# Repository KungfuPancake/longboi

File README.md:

# Longboi AFC controller

Tired of the mess of cables in your BoxTurtle? Want to add a heated filament dryer chamber some time down the road? Want to control that cooling fan with PWM? This project is for you!

The Longboi sits behind the full width of the BoxTurtle front panel and allows very short cable runs of equal length from each respooler and extruder. It's equipped with a beefy STM32H723 MCU and can be controlled with CAN or USB. If using CAN it's also daisy chainable for 8, 12 or even more lanes!

# How to get a Longboi

## Buying a complete board
LDO will sell complete boards via various resellers. Production is currently unknown - check back later for updates!

## PCB + Assembly by JLCPCB
You can order assembled PCBs from pretty much any fab, although currently only production files tested with JLCPCB are available in [jlcpcb/](https://github.com/KungfuPancake/longboi/tree/main/jlcpcb).
To order PCBs with assembly you'll have to go through their manufacturing wizard, using mostly standard settings. Although the JLC engineers will try and correct any mistakes, please do sanity checks on every page.
1. Upload `longboi.zip`into the PCB quote form and select a quantity. Five PCBs is the minimum quantity, cost per board will be lower the more boards you order since most of the cost is setup fees. Select a solder mask color you like - green is usually cheapest. I highly recommend choosing ENIG as a surface finish, HASL is usually not worth the saved money on production boards. Leave all other settings on their default values. Check PCBA (assembly) on the bottom of the form. Click "Next".
2. Check if the PCB looks like it should, then click "Next".
3. Upload `bom.csv` for BOM, `positions.csv`for CPL. Click "Next".
4. Check if all components look right, if there are stock shortages you will have to select replacement. Be very careful to select components that are equal or better in specs. If everything looks good, click "Next".
5. Check the placement of all components, especially if the first pin corresponds with the PCB markings. Slight inaccuracies on the big through hole connectors are okay, as they are hand soldered anyway. Click "Next".
6. You'll see a breakdown of all individual fees and prices. If you're flexible on the amount of PCBs you order you can try and see which amount has the best value to you.
7. Done!

Please be aware that the BOM only contains a fuse holder, the fuses (2410/1808) have to be sourced separately. 4A is a good value to start, depending on the heater you may or may not use the value can be scaled up or down accordingly.

## PCB + assembling it yourself
Order the PCBs anywere you want as the specs are very modest. Assembly of the board is an advanced task requiring lots of soldering, including hot air and/or using a reflow oven. If you don't feel comfortable with that, you should let the fab handle the assembly.

Please be aware that the BOM only contains a fuse holder, the fuses (2410/1808) have to be sourced separately. 4A is a good value to start, depending on the heater you may or may not use the value can be scaled up or down accordingly.

# Preparations
This is a general guideline how to proceed with flashing the Katapult bootloader (optional) and Klipper. If you struggle with the process or encounter errors on the way, especially when using CAN bus, try the detailed instructions and troubleshooting tips and tricks from [Esoterical's CANBus guide](https://canbus.esoterical.online/).
Start with only USB connected via the JST header. When plugging in the USB cable into your computer, the 3.3V and USB LEDs should light up. Now you're ready for flashing!

## CAN
### Katapult

### Klipper

## USB
### Katapult

### Klipper

## Initial flash via DFU
To enable CAN or USB flashing via Katapult or Klipper you'll have to bootstrap the board via the MCUs built-in DFU bootloader, using dfu-util. To enter the DFU bootloader, hold down the "Boot"-button, then press the "Reset"-button shortly. You can now release both buttons and the Longboi should be visible as a "STM Device in DFU Mode" USB device.

Use dfu-util to flash the desired firmware, e.g. Katapult: ```dfu-util -R -a 0 -s 0x08000000:leave -D ~/katapult/out/katapult.bin -d 0483:df11```

## Flashing Katapult and/or Klipper
When using USB, flashing Katapult is not needed as Klipper can update its own firmware. Go through the Klipper build steps using the configuration from above, then flash klipper.bin using dfu-util. From now on you can update Klipper directly with ```make flash FLASH_DEVICE={your device path}```

If you're using a CAN setup and need to use Katapult, build it with the configuration from above and flash it via ```dfu-util```. You may have to reset the board with the "Reset"-button after flashing, the "Info"-LED should be blinking now. If it doesn't, try manually entering Katapult by double-clicking "Reset". Once Katapult is running, all flash operations have to be done via CAN bus. Remove the USB cable from the board and attach it to your CAN bus using a suitable cable. Remember to power down your printer before connecting anything!

If everything went well, Katapult should be visible with the flash tool: ```~/katapult/scripts/flashtool.py -i can0 -q```

You can now flash Klipper: ```~/katapult/scripts/flashtool.py -f ~/klipper/out/klipper.bin -u {your address}```

And you're done!

## Print parts
### Base BoxTurtle
BOM:
* ~95g of primary color filament
* 7x M3x4x5 heat set insert (Voron style)
* 7x M3x10 SHCS
* (Optional) 7x M3x5 brass standoffs
* (Optional) 7x M3x4 SHCS

Print the following parts in your primary color:

* 1x skirt_front_hex_single.stl (no split parts available yet)

If you're not using brass standoffs, also print:

* 7x pcb_spacer_x7.stl

Print all parts using the BoxTurtle settings, make sure that you tuned your filament for shrinkage as the mounting holes won't line up otherwise.

### BoxTurtle Enclosure
Please use the CAD files for reference until a detailed manual is available.

# Assembly
## Mounting PCB + front skirt
### Base BoxTurtle
Add the heat set inserts into the front skirt, then mount the PCB. If you're using brass standoffs, screw those in first, then mount the board using the M3x4 fasteners. If using printed spacers, for easier assembly you can pre-insert two M3x10s into the PCB, add spacers and then mount it on the front skirt. Then use tweezers to add spacers between the PCB and the skirt on the remaining holes and add the rest of the M3x10s.
Insert the front skirt according to the manual and double check that the cutouts on the PCB correspond to the respooler switch tabs.

### BoxTurtle Enclosure
Please use the CAD files for reference until a detailed manual is available.

## Connections
Every respooler + extruder has its own set of connectors on the PCB, e.g. M4, RGB4, S8, S7, STP4.

If you're making your own cables, to make your life easier, assemble one respooler and one extruder first with generous cable length. Mount everything, measure everything, cut and crimp all connections. Afterwards, remove the respooler and extruder and finish the other three sets outside of the BoxTurtle with your measurements.
Tidy up with cable ties/velcro straps as needed and plug in everything.

# Configuration
## Pin aliases / longboi.cfg
coming soon
## AFC configuration
coming soon

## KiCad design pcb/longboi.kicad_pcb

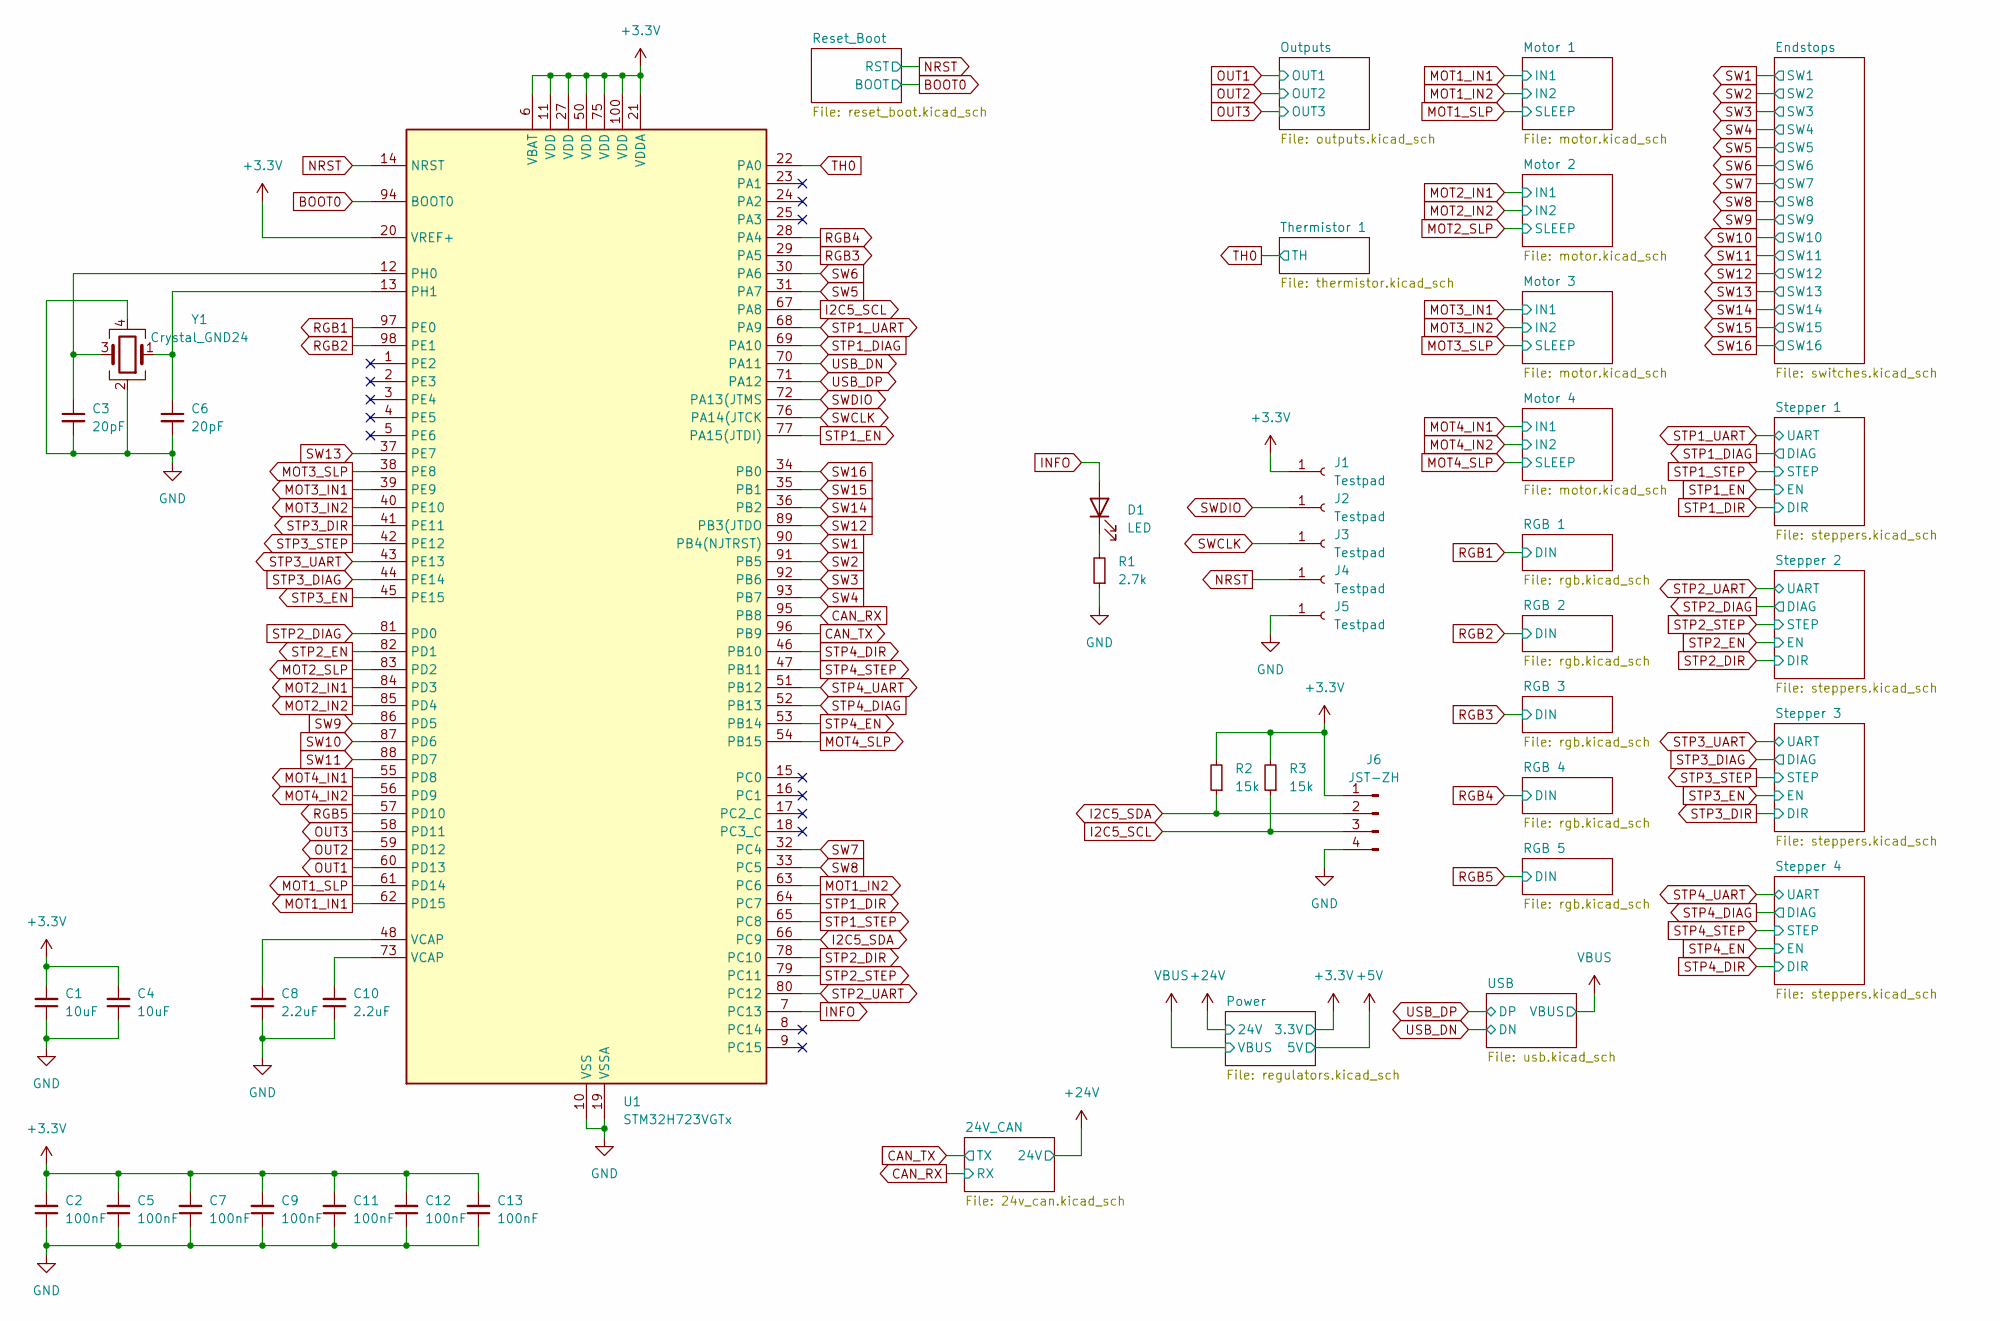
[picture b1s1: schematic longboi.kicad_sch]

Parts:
C1, C4: 10uF; C_0603_1608Metric
C2, C5, C7, C9, C11, C12, C13: 100nF; C_0603_1608Metric
C3, C6: 20pF; C_0603_1608Metric
C8, C10: 2.2uF; C_0603_1608Metric
D1: LED; LED_0603_1608Metric
J1, J2, J3, J4, J5: Testpad; TestPoint_THTPad_D1.0mm_Drill0.5mm
J6: JST-ZH; JST_ZH_B4B-ZR_1x04_P1.50mm_Vertical
R1: 2.7k; R_0603_1608Metric
R2, R3: 15k; R_0603_1608Metric
U1: STM32H723VGTx; LQFP-100_14x14mm_P0.5mm
Y1: Crystal_GND24; Crystal_SMD_3225-4Pin_3.2x2.5mm

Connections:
+3.3V: C1.2, C2.2, C4.2, C5.2, C7.2, C9.2, C11.2, C12.2, C13.2, J1.1, J6.1, R2.2, R3.2, U1.6 (VBAT), U1.11 (VDD), U1.20 (VREF+), U1.21 (VDDA), U1.27 (VDD), U1.50 (VDD), U1.75 (VDD), U1.100 (VDD); also elsewhere on the board
BOOT0: U1.94 (BOOT0); also elsewhere on the board
CAN_RX: U1.95 (PB8); also elsewhere on the board
CAN_TX: U1.96 (PB9); also elsewhere on the board
GND: C1.1, C2.1, C3.2, C4.1, C5.1, C6.2, C7.1, C8.1, C9.1, C10.1, C11.1, C12.1, C13.1, J5.1, J6.4, R1.1, U1.10 (VSS), U1.19 (VSSA), U1.26 (VSS), U1.49 (VSS), U1.74 (VSS), U1.99 (VSS), Y1.2, Y1.4; also elsewhere on the board
I2C5_SCL: J6.3, R3.1, U1.67 (PA8)
I2C5_SDA: J6.2, R2.1, U1.66 (PC9)
INFO: D1.2 (A), U1.7 (PC13)
MOT1_IN1: U1.62 (PD15); also elsewhere on the board
MOT1_IN2: U1.63 (PC6); also elsewhere on the board
MOT1_SLP: U1.61 (PD14); also elsewhere on the board
MOT2_IN1: U1.84 (PD3); also elsewhere on the board
MOT2_IN2: U1.85 (PD4); also elsewhere on the board
MOT2_SLP: U1.83 (PD2); also elsewhere on the board
MOT3_IN1: U1.39 (PE9); also elsewhere on the board
MOT3_IN2: U1.40 (PE10); also elsewhere on the board
MOT3_SLP: U1.38 (PE8); also elsewhere on the board
MOT4_IN1: U1.55 (PD8); also elsewhere on the board
MOT4_IN2: U1.56 (PD9); also elsewhere on the board
MOT4_SLP: U1.54 (PB15); also elsewhere on the board
NRST: J4.1, U1.14 (NRST); also elsewhere on the board
unnamed: C8.2, U1.48 (VCAP)
unnamed: C10.2, U1.73 (VCAP)
unnamed: D1.1 (K), R1.2
unnamed: C3.1, U1.12 (PH0), Y1.3
unnamed: C6.1, U1.13 (PH1), Y1.1
OUT1: U1.60 (PD13); also elsewhere on the board
OUT2: U1.59 (PD12); also elsewhere on the board
OUT3: U1.58 (PD11); also elsewhere on the board
RGB1: U1.97 (PE0); also elsewhere on the board
RGB2: U1.98 (PE1); also elsewhere on the board
RGB3: U1.29 (PA5); also elsewhere on the board
RGB4: U1.28 (PA4); also elsewhere on the board
RGB5: U1.57 (PD10); also elsewhere on the board
STP1_DIAG: U1.69 (PA10); also elsewhere on the board
STP1_DIR: U1.64 (PC7); also elsewhere on the board
STP1_EN: U1.77 (PA15(JTDI)); also elsewhere on the board
STP1_STEP: U1.65 (PC8); also elsewhere on the board
STP1_UART: U1.68 (PA9); also elsewhere on the board
STP2_DIAG: U1.81 (PD0); also elsewhere on the board
STP2_DIR: U1.78 (PC10); also elsewhere on the board
STP2_EN: U1.82 (PD1); also elsewhere on the board
STP2_STEP: U1.79 (PC11); also elsewhere on the board
STP2_UART: U1.80 (PC12); also elsewhere on the board
STP3_DIAG: U1.44 (PE14); also elsewhere on the board
STP3_DIR: U1.41 (PE11); also elsewhere on the board
STP3_EN: U1.45 (PE15); also elsewhere on the board
STP3_STEP: U1.42 (PE12); also elsewhere on the board
STP3_UART: U1.43 (PE13); also elsewhere on the board
STP4_DIAG: U1.52 (PB13); also elsewhere on the board
STP4_DIR: U1.46 (PB10); also elsewhere on the board
STP4_EN: U1.53 (PB14); also elsewhere on the board
STP4_STEP: U1.47 (PB11); also elsewhere on the board
STP4_UART: U1.51 (PB12); also elsewhere on the board
SW1: U1.90 (PB4(NJTRST)); also elsewhere on the board
SW2: U1.91 (PB5); also elsewhere on the board
SW3: U1.92 (PB6); also elsewhere on the board
SW4: U1.93 (PB7); also elsewhere on the board
SW5: U1.31 (PA7); also elsewhere on the board
SW6: U1.30 (PA6); also elsewhere on the board
SW7: U1.32 (PC4); also elsewhere on the board
SW8: U1.33 (PC5); also elsewhere on the board
SW9: U1.86 (PD5); also elsewhere on the board
SW10: U1.87 (PD6); also elsewhere on the board
SW11: U1.88 (PD7); also elsewhere on the board
SW12: U1.89 (PB3(JTDO); also elsewhere on the board
SW13: U1.37 (PE7); also elsewhere on the board
SW14: U1.36 (PB2); also elsewhere on the board
SW15: U1.35 (PB1); also elsewhere on the board
SW16: U1.34 (PB0); also elsewhere on the board
SWCLK: J3.1, U1.76 (PA14(JTCK)
SWDIO: J2.1, U1.72 (PA13(JTMS)
TH0: U1.22 (PA0); also elsewhere on the board
USB_DN: U1.70 (PA11); also elsewhere on the board
USB_DP: U1.71 (PA12); also elsewhere on the board

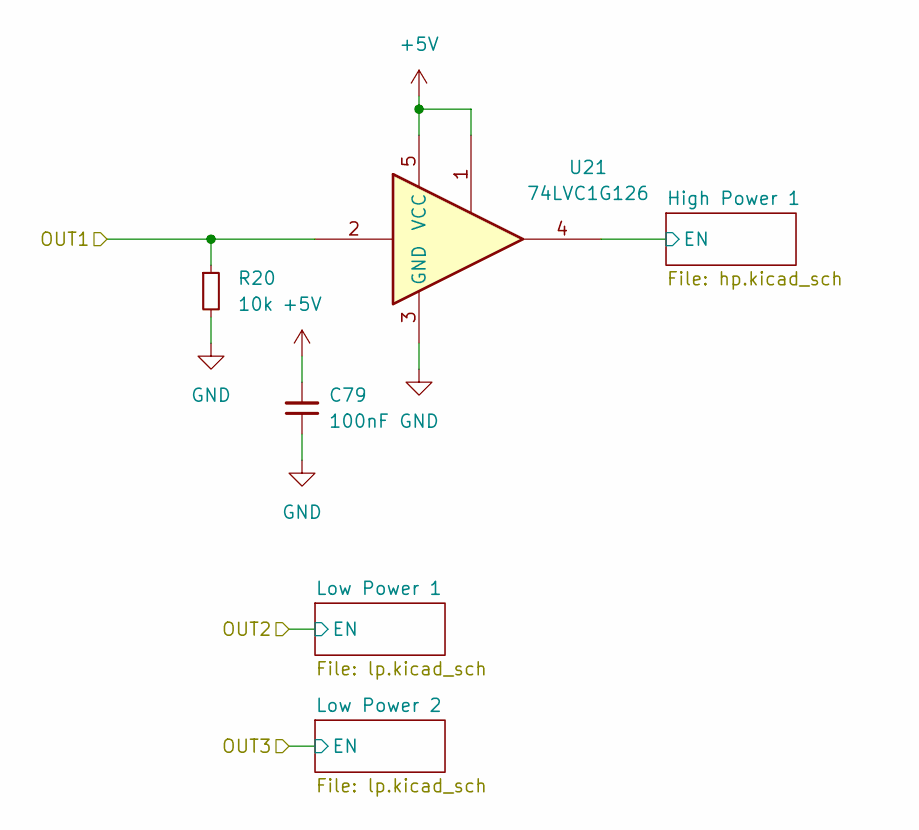
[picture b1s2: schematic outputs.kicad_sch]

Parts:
C79: 100nF; C_0603_1608Metric
R20: 10k; R_0603_1608Metric
U21: 74LVC1G126; SOT-353_SC-70-5

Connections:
+5V: C79.2, U21.1, U21.5 (VCC); also elsewhere on the board
/Outputs/High Power 1/EN: U21.4; also elsewhere on the board
GND: C79.1, R20.2, U21.3 (GND); also elsewhere on the board
OUT1: R20.1, U21.2; also elsewhere on the board

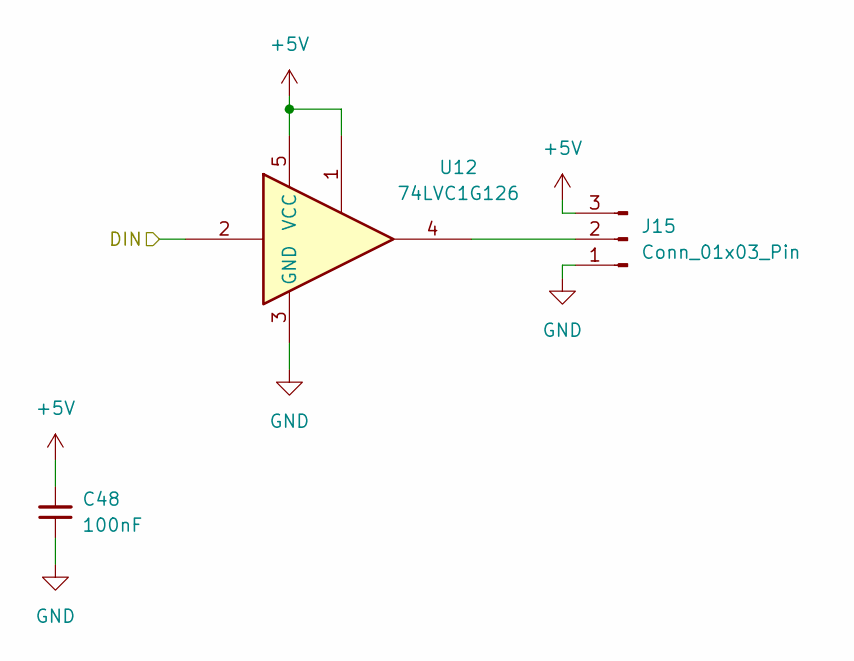
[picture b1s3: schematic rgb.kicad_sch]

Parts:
C48: 100nF; C_0603_1608Metric; LCSC C14663
J15: Conn_01x03_Pin; JST_XH_B3B-XH-A_1x03_P2.50mm_Vertical; LCSC C565985
U12: 74LVC1G126; SOT-353_SC-70-5; LCSC C7394032

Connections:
+5V: C48.2, J15.3, U12.1, U12.5 (VCC); also elsewhere on the board
GND: C48.1, J15.1, U12.3 (GND); also elsewhere on the board
unnamed: J15.2, U12.4
RGB1: U12.2; also elsewhere on the board

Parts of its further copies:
C49, C50, C51, C80: 100nF; C_0603_1608Metric; LCSC C14663
J16, J17, J18, J40: Conn_01x03_Pin; JST_XH_B3B-XH-A_1x03_P2.50mm_Vertical; LCSC C565985
U13, U14, U15, U22: 74LVC1G126; SOT-353_SC-70-5; LCSC C7394032

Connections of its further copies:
+5V: C49.2, C50.2, C51.2, C80.2, J16.3, J17.3, J18.3, J40.3, U13.1, U13.5 (VCC), U14.1, U14.5 (VCC), U15.1, U15.5 (VCC), U22.1, U22.5 (VCC); also elsewhere on the board
GND: C49.1, C50.1, C51.1, C80.1, J16.1, J17.1, J18.1, J40.1, U13.3 (GND), U14.3 (GND), U15.3 (GND), U22.3 (GND); also elsewhere on the board
unnamed: J16.2, U13.4
unnamed: J17.2, U14.4
unnamed: J18.2, U15.4
unnamed: J40.2, U22.4
RGB2: U13.2; also elsewhere on the board
RGB3: U14.2; also elsewhere on the board
RGB4: U15.2; also elsewhere on the board
RGB5: U22.2; also elsewhere on the board

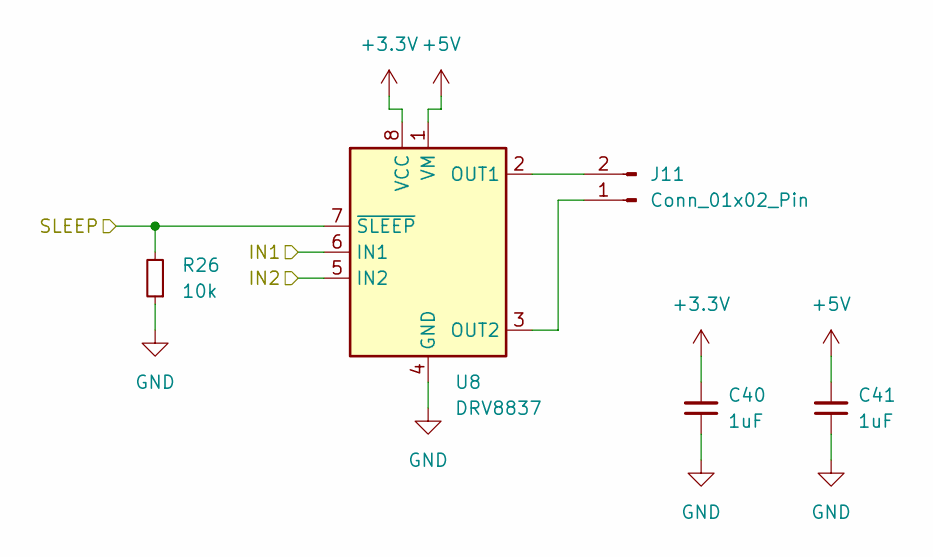
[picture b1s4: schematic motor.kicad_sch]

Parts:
C40, C41: 1uF; C_0603_1608Metric
J11: Conn_01x02_Pin; JST_XH_B2B-XH-A_1x02_P2.50mm_Vertical
R26: 10k; R_0603_1608Metric
U8: DRV8837; WSON-8-1EP_2x2mm_P0.5mm_EP0.9x1.6mm

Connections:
+3.3V: C40.2, U8.8 (VCC); also elsewhere on the board
+5V: C41.2, U8.1 (VM); also elsewhere on the board
GND: C40.1, C41.1, R26.1, U8.4 (GND), U8.9 (GND); also elsewhere on the board
MOT1_IN1: U8.6 (IN1); also elsewhere on the board
MOT1_IN2: U8.5 (IN2); also elsewhere on the board
MOT1_SLP: R26.2, U8.7 (~SLEEP); also elsewhere on the board
unnamed: J11.1, U8.3 (OUT2)
unnamed: J11.2, U8.2 (OUT1)

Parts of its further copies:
C42, C43, C44, C45, C46, C47: 1uF; C_0603_1608Metric
J12, J13, J14: Conn_01x02_Pin; JST_XH_B2B-XH-A_1x02_P2.50mm_Vertical
R27, R67, R68: 10k; R_0603_1608Metric
U9, U10, U11: DRV8837; WSON-8-1EP_2x2mm_P0.5mm_EP0.9x1.6mm

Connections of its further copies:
+3.3V: C42.2, C44.2, C46.2, U9.8 (VCC), U10.8 (VCC), U11.8 (VCC); also elsewhere on the board
+5V: C43.2, C45.2, C47.2, U9.1 (VM), U10.1 (VM), U11.1 (VM); also elsewhere on the board
GND: C42.1, C43.1, C44.1, C45.1, C46.1, C47.1, R27.1, R67.1, R68.1, U9.4 (GND), U9.9 (GND), U10.4 (GND), U10.9 (GND), U11.4 (GND), U11.9 (GND); also elsewhere on the board
MOT2_IN1: U9.6 (IN1); also elsewhere on the board
MOT2_IN2: U9.5 (IN2); also elsewhere on the board
MOT2_SLP: R27.2, U9.7 (~SLEEP); also elsewhere on the board
MOT3_IN1: U10.6 (IN1); also elsewhere on the board
MOT3_IN2: U10.5 (IN2); also elsewhere on the board
MOT3_SLP: R67.2, U10.7 (~SLEEP); also elsewhere on the board
MOT4_IN1: U11.6 (IN1); also elsewhere on the board
MOT4_IN2: U11.5 (IN2); also elsewhere on the board
MOT4_SLP: R68.2, U11.7 (~SLEEP); also elsewhere on the board
unnamed: J12.1, U9.3 (OUT2)
unnamed: J12.2, U9.2 (OUT1)
unnamed: J13.1, U10.3 (OUT2)
unnamed: J13.2, U10.2 (OUT1)
unnamed: J14.1, U11.3 (OUT2)
unnamed: J14.2, U11.2 (OUT1)

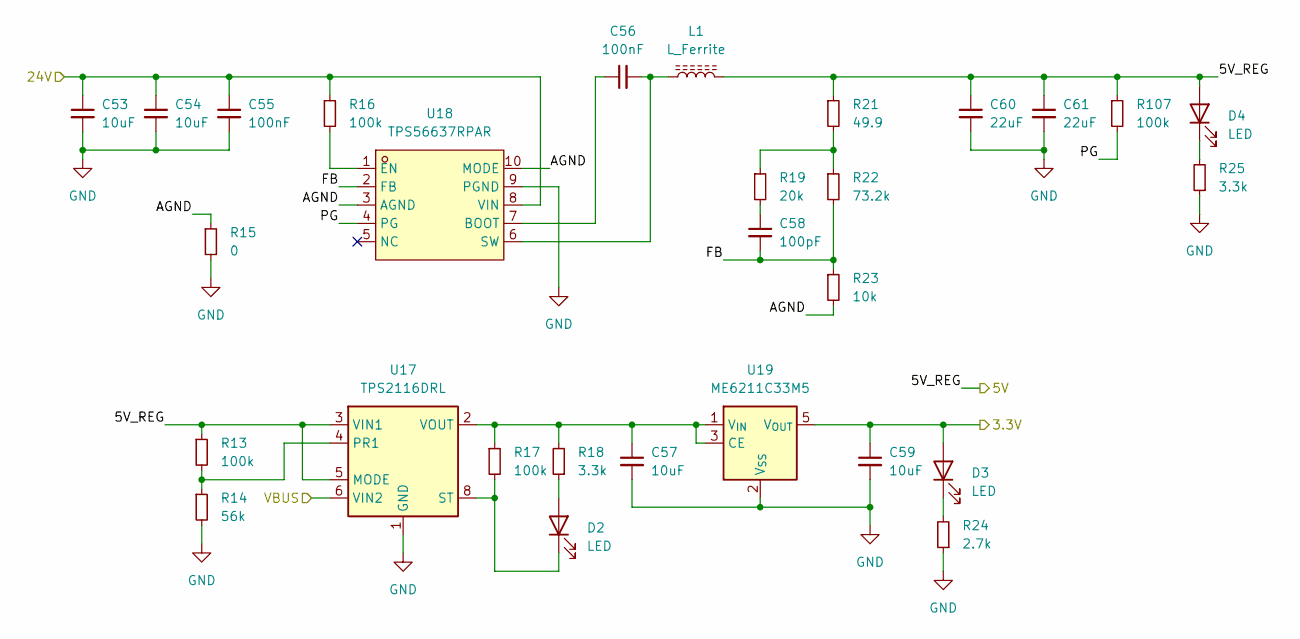
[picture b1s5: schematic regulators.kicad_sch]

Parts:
C53, C54: 10uF; C_1206_3216Metric
C55, C56: 100nF; C_0603_1608Metric
C57, C59: 10uF; C_0603_1608Metric
C58: 100pF; C_0603_1608Metric
C60, C61: 22uF; C_0805_2012Metric
D2, D3, D4: LED; LED_0603_1608Metric
L1: L_Ferrite; L_Chilisin_BMRA00050530
R13, R16, R17, R107: 100k; R_0603_1608Metric
R14: 56k; R_0603_1608Metric
R15: 0; R_0603_1608Metric
R18, R25: 3.3k; R_0603_1608Metric
R19: 20k; R_0603_1608Metric
R21: 49.9; R_0603_1608Metric
R22: 73.2k; R_0603_1608Metric
R23: 10k; R_0603_1608Metric
R24: 2.7k; R_0603_1608Metric
U17: TPS2116DRL; SOT-583-8
U18: TPS56637RPAR; VQFN-HR-10_L3.0-W3.0_RPA; LCSC Part C841386
U19: ME6211C33M5; SOT-23-5

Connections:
+3.3V: C59.1, D3.2 (A), U19.5 (V_{OUT}); also elsewhere on the board
+5V: C60.1, C61.1, D4.2 (A), L1.2, R13.1, R21.1, R107.1, U17.3 (VIN1), U17.5 (MODE); also elsewhere on the board
+24V: C53.1, C54.1, C55.1, R16.1, U18.8 (VIN); also elsewhere on the board
/Power/AGND: R15.1, R23.2, U18.3 (AGND), U18.10 (MODE)
/Power/FB: C58.2, R22.2, R23.1, U18.2 (FB)
/Power/PG: R107.2, U18.4 (PG)
GND: C53.2, C54.2, C55.2, C57.2, C59.2, C60.2, C61.2, R14.2, R15.2, R24.1, R25.1, U17.1 (GND), U18.9 (PGND), U19.2 (V_{SS}); also elsewhere on the board
unnamed: C58.1, R19.2
unnamed: D2.2 (A), R18.1
unnamed: D2.1 (K), R17.2, U17.8 (ST)
unnamed: D3.1 (K), R24.2
unnamed: D4.1 (K), R25.2
unnamed: R19.1, R21.2, R22.1
unnamed: R13.2, R14.1, U17.4 (PR1)
unnamed: C56.1, U18.7 (BOOT)
unnamed: R16.2, U18.1 (EN)
unnamed: C56.2, L1.1, U18.6 (SW)
unnamed: C57.1, R17.1, R18.2, U17.2 (VOUT), U17.7 (VOUT), U19.1 (V_{IN}), U19.3 (CE)
VBUS: U17.6 (VIN2); also elsewhere on the board

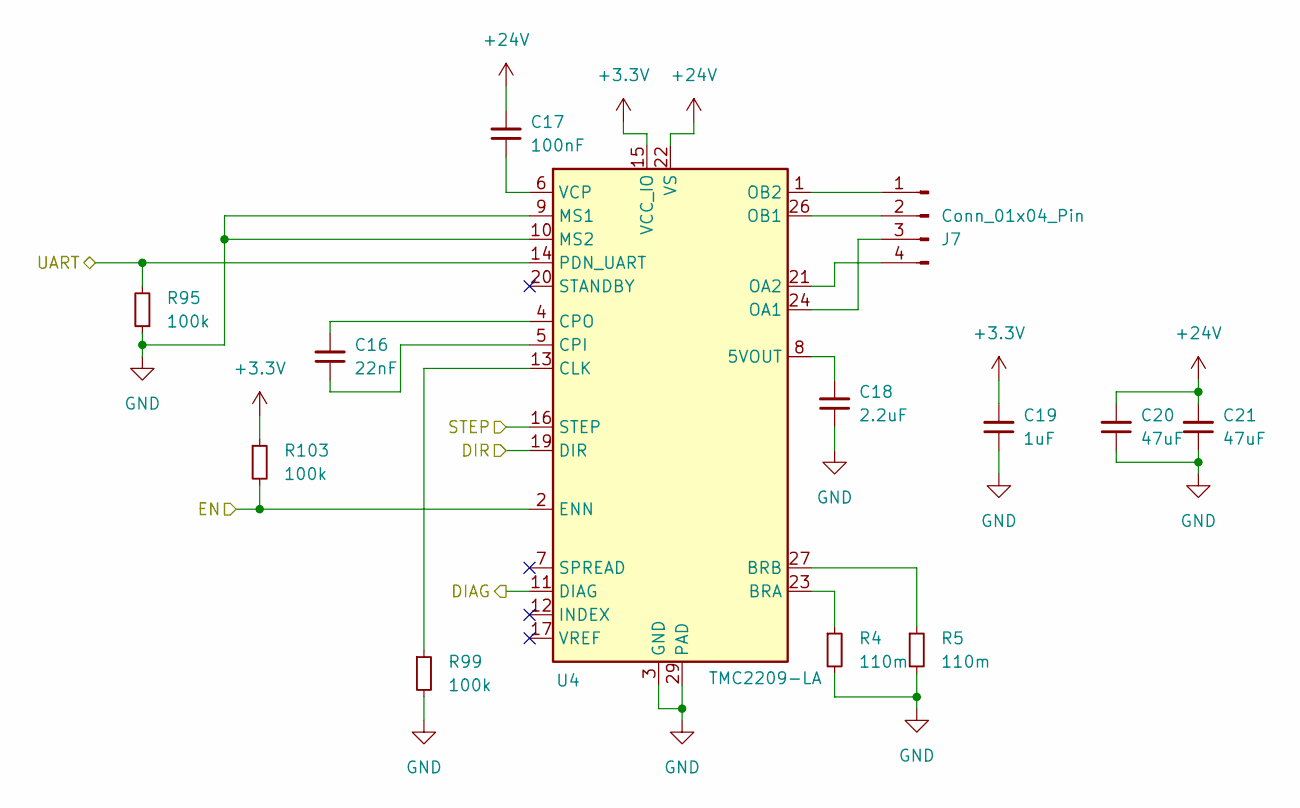
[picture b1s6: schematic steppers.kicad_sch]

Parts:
C16: 22nF; C_0603_1608Metric
C17: 100nF; C_0603_1608Metric
C18: 2.2uF; C_0603_1608Metric
C19: 1uF; C_0603_1608Metric
C20, C21: 47uF; C_1210_3225Metric
J7: Conn_01x04_Pin; JST_XH_B4B-XH-A_1x04_P2.50mm_Vertical
R4, R5: 110m; R_1206_3216Metric
R95, R99, R103: 100k; R_0603_1608Metric
U4: TMC2209-LA; QFN-28-1EP_5x5mm_P0.5mm_EP3.75x3.75mm_ThermalVias

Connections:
+3.3V: C19.2, R103.1, U4.15 (VCC_IO); also elsewhere on the board
+24V: C17.2, C20.2, C21.2, U4.22 (VS), U4.28 (VS); also elsewhere on the board
GND: C18.1, C19.1, C20.1, C21.1, R4.2, R5.2, R95.1, R99.2, U4.3 (GND), U4.9 (MS1), U4.10 (MS2), U4.18 (GND), U4.29 (PAD); also elsewhere on the board
unnamed: J7.1, U4.1 (OB2)
unnamed: J7.2, U4.26 (OB1)
unnamed: J7.3, U4.24 (OA1)
unnamed: J7.4, U4.21 (OA2)
unnamed: C18.2, U4.8 (5VOUT)
unnamed: R4.1, U4.23 (BRA)
unnamed: R5.1, U4.27 (BRB)
unnamed: R99.1, U4.13 (CLK)
unnamed: C16.1, U4.5 (CPI)
unnamed: C16.2, U4.4 (CPO)
unnamed: C17.1, U4.6 (VCP)
STP1_DIAG: U4.11 (DIAG); also elsewhere on the board
STP1_DIR: U4.19 (DIR); also elsewhere on the board
STP1_EN: R103.2, U4.2 (ENN); also elsewhere on the board
STP1_STEP: U4.16 (STEP); also elsewhere on the board
STP1_UART: R95.2, U4.14 (PDN_UART); also elsewhere on the board

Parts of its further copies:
C22, C28, C34: 22nF; C_0603_1608Metric
C23, C29, C35: 100nF; C_0603_1608Metric
C24, C30, C36: 2.2uF; C_0603_1608Metric
C25, C31, C37: 1uF; C_0603_1608Metric
C26, C27, C32, C33, C38, C39: 47uF; C_1210_3225Metric
J8, J9, J10: Conn_01x04_Pin; JST_XH_B4B-XH-A_1x04_P2.50mm_Vertical
R6, R7, R8, R9, R10, R11: 110m; R_1206_3216Metric
R96, R97, R98, R100, R101, R102, R104, R105, R106: 100k; R_0603_1608Metric
U5, U6, U7: TMC2209-LA; QFN-28-1EP_5x5mm_P0.5mm_EP3.75x3.75mm_ThermalVias

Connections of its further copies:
+3.3V: C25.2, C31.2, C37.2, R104.1, R105.1, R106.1, U5.15 (VCC_IO), U6.15 (VCC_IO), U7.15 (VCC_IO); also elsewhere on the board
+24V: C23.2, C26.2, C27.2, C29.2, C32.2, C33.2, C35.2, C38.2, C39.2, U5.22 (VS), U5.28 (VS), U6.22 (VS), U6.28 (VS), U7.22 (VS), U7.28 (VS); also elsewhere on the board
GND: C24.1, C25.1, C26.1, C27.1, C30.1, C31.1, C32.1, C33.1, C36.1, C37.1, C38.1, C39.1, R6.2, R7.2, R8.2, R9.2, R10.2, R11.2, R96.1, R97.1, R98.1, R100.2, R101.2, R102.2, U5.3 (GND), U5.9 (MS1), U5.10 (MS2), U5.18 (GND), U5.29 (PAD), U6.3 (GND), U6.9 (MS1), U6.10 (MS2), U6.18 (GND), U6.29 (PAD), U7.3 (GND), U7.9 (MS1), U7.10 (MS2), U7.18 (GND), U7.29 (PAD); also elsewhere on the board
unnamed: J8.1, U5.1 (OB2)
unnamed: J8.2, U5.26 (OB1)
unnamed: J8.3, U5.24 (OA1)
unnamed: J8.4, U5.21 (OA2)
unnamed: J9.1, U6.1 (OB2)
unnamed: J9.2, U6.26 (OB1)
unnamed: J9.3, U6.24 (OA1)
unnamed: J9.4, U6.21 (OA2)
unnamed: J10.1, U7.1 (OB2)
unnamed: J10.2, U7.26 (OB1)
unnamed: J10.3, U7.24 (OA1)
unnamed: J10.4, U7.21 (OA2)
unnamed: C24.2, U5.8 (5VOUT)
unnamed: R6.1, U5.23 (BRA)
unnamed: R7.1, U5.27 (BRB)
unnamed: R100.1, U5.13 (CLK)
unnamed: C22.1, U5.5 (CPI)
unnamed: C22.2, U5.4 (CPO)
unnamed: C23.1, U5.6 (VCP)
unnamed: C30.2, U6.8 (5VOUT)
unnamed: R8.1, U6.23 (BRA)
unnamed: R9.1, U6.27 (BRB)
unnamed: R101.1, U6.13 (CLK)
unnamed: C28.1, U6.5 (CPI)
unnamed: C28.2, U6.4 (CPO)
unnamed: C29.1, U6.6 (VCP)
unnamed: C36.2, U7.8 (5VOUT)
unnamed: R10.1, U7.23 (BRA)
unnamed: R11.1, U7.27 (BRB)
unnamed: R102.1, U7.13 (CLK)
unnamed: C34.1, U7.5 (CPI)
unnamed: C34.2, U7.4 (CPO)
unnamed: C35.1, U7.6 (VCP)
STP2_DIAG: U5.11 (DIAG); also elsewhere on the board
STP2_DIR: U5.19 (DIR); also elsewhere on the board
STP2_EN: R104.2, U5.2 (ENN); also elsewhere on the board
STP2_STEP: U5.16 (STEP); also elsewhere on the board
STP2_UART: R96.2, U5.14 (PDN_UART); also elsewhere on the board
STP3_DIAG: U6.11 (DIAG); also elsewhere on the board
STP3_DIR: U6.19 (DIR); also elsewhere on the board
STP3_EN: R105.2, U6.2 (ENN); also elsewhere on the board
STP3_STEP: U6.16 (STEP); also elsewhere on the board
STP3_UART: R97.2, U6.14 (PDN_UART); also elsewhere on the board
STP4_DIAG: U7.11 (DIAG); also elsewhere on the board
STP4_DIR: U7.19 (DIR); also elsewhere on the board
STP4_EN: R106.2, U7.2 (ENN); also elsewhere on the board
STP4_STEP: U7.16 (STEP); also elsewhere on the board
STP4_UART: R98.2, U7.14 (PDN_UART); also elsewhere on the board

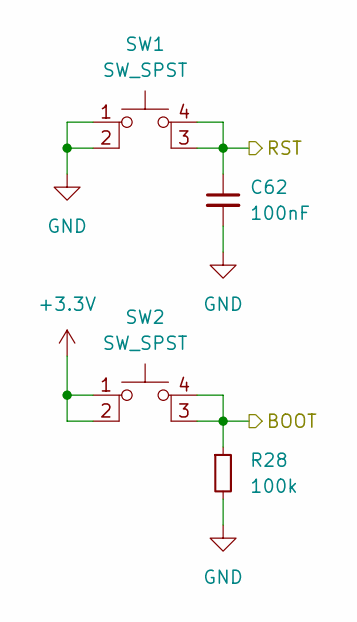
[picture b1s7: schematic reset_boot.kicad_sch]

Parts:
C62: 100nF; C_0603_1608Metric
R28: 100k; R_0603_1608Metric
SW1, SW2: SW_SPST; SW-SMD_4P-L3.4-W3.4-P2.00-LS4.0_TS3315A160GF

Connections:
+3.3V: SW2.1, SW2.2; also elsewhere on the board
BOOT0: R28.1, SW2.3 (K), SW2.4 (A); also elsewhere on the board
GND: C62.2, R28.2, SW1.1, SW1.2; also elsewhere on the board
NRST: C62.1, SW1.3 (K), SW1.4 (A); also elsewhere on the board

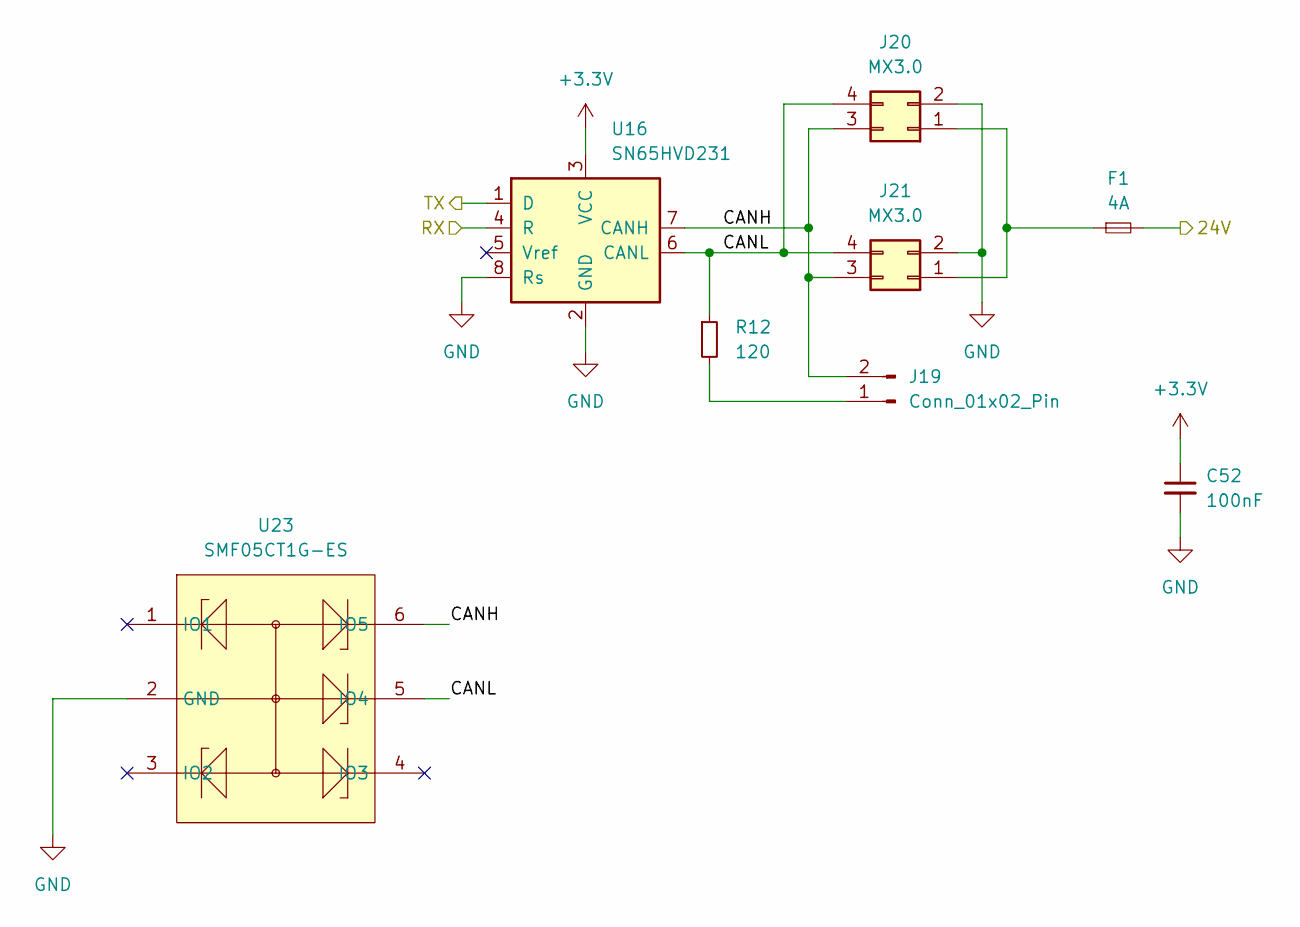
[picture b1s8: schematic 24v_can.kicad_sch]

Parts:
C52: 100nF; C_0603_1608Metric
F1: 4A; Fuseholder_Littelfuse_Nano2_154x
J19: Conn_01x02_Pin; PinHeader_1x02_P2.54mm_Vertical
J20, J21: MX3.0; Molex_Micro-Fit_3.0_43045-0412_2x02_P3.00mm_Vertical
R12: 120; R_0603_1608Metric
U16: SN65HVD231; SOIC-8_3.9x4.9mm_P1.27mm
U23: SMF05CT1G-ES; SOT-363_SC-70-6; LCSC Part C5180312

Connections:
+3.3V: C52.1, U16.3 (VCC); also elsewhere on the board
+24V: F1.2; also elsewhere on the board
/24V_CAN/CANH: J19.2, J20.3, J21.3, U16.7 (CANH), U23.6 (IO5)
/24V_CAN/CANL: J20.4, J21.4, R12.1, U16.6 (CANL), U23.5 (IO4)
CAN_RX: U16.4 (R); also elsewhere on the board
CAN_TX: U16.1 (D); also elsewhere on the board
GND: C52.2, J20.2, J21.2, U16.2 (GND), U16.8 (Rs), U23.2 (GND); also elsewhere on the board
unnamed: J19.1, R12.2
unnamed: F1.1, J20.1, J21.1

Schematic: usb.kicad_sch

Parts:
J42: JST-ZH; JST_ZH_B4B-ZR_1x04_P1.50mm_Vertical; LCSC C157997
U20: SMF05CT1G-ES; SOT-363_SC-70-6; LCSC Part C5180312

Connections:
GND: J42.4, U20.2 (GND); also elsewhere on the board
USB_DN: J42.2, U20.1 (IO1); also elsewhere on the board
USB_DP: J42.3, U20.6 (IO5); also elsewhere on the board
VBUS: J42.1, U20.5 (IO4); also elsewhere on the board

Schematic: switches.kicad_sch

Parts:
C14, C15: 100nF; C_0603_1608Metric
RN1, RN2, RN3, RN4: 10k; R_Array_Convex_4x0603
U2, U3: SN74LVC245APW; TSSOP-20_4.4x6.5mm_P0.65mm

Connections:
+3.3V: C14.1, C15.1, RN1.5 (R4.2), RN1.6 (R3.2), RN1.7 (R2.2), RN1.8 (R1.2), RN2.5 (R4.2), RN2.6 (R3.2), RN2.7 (R2.2), RN2.8 (R1.2), RN3.5 (R4.2), RN3.6 (R3.2), RN3.7 (R2.2), RN3.8 (R1.2), RN4.5 (R4.2), RN4.6 (R3.2), RN4.7 (R2.2), RN4.8 (R1.2), U2.1 (DIR), U2.20 (VCC), U3.1 (DIR), U3.20 (VCC); also elsewhere on the board
/Endstops/Switch 1/SW: U3.6 (A5); also elsewhere on the board
/Endstops/Switch 2/SW: U3.7 (A6); also elsewhere on the board
/Endstops/Switch 3/SW: U3.9 (A8); also elsewhere on the board
/Endstops/Switch 4/SW: U3.8 (A7); also elsewhere on the board
/Endstops/Switch 5/SW: U2.3 (A2); also elsewhere on the board
/Endstops/Switch 6/SW: U2.2 (A1); also elsewhere on the board
/Endstops/Switch 7/SW: U2.4 (A3); also elsewhere on the board
/Endstops/Switch 8/SW: U2.5 (A4); also elsewhere on the board
/Endstops/Switch 9/SW: U3.2 (A1); also elsewhere on the board
/Endstops/Switch 10/SW: U3.3 (A2); also elsewhere on the board
/Endstops/Switch 11/SW: U3.4 (A3); also elsewhere on the board
/Endstops/Switch 12/SW: U3.5 (A4); also elsewhere on the board
/Endstops/Switch 13/SW: U2.9 (A8); also elsewhere on the board
/Endstops/Switch 14/SW: U2.8 (A7); also elsewhere on the board
/Endstops/Switch 15/SW: U2.7 (A6); also elsewhere on the board
/Endstops/Switch 16/SW: U2.6 (A5); also elsewhere on the board
GND: C14.2, C15.2, U2.10 (GND), U2.19 (~OE), U3.10 (GND), U3.19 (~OE); also elsewhere on the board
SW1: RN4.1 (R1.1), U3.14 (B5); also elsewhere on the board
SW2: RN4.2 (R2.1), U3.13 (B6); also elsewhere on the board
SW3: RN4.3 (R3.1), U3.12 (B7); also elsewhere on the board
SW4: RN4.4 (R4.1), U3.11 (B8); also elsewhere on the board
SW5: RN1.2 (R2.1), U2.17 (B2); also elsewhere on the board
SW6: RN1.1 (R1.1), U2.18 (B1); also elsewhere on the board
SW7: RN1.3 (R3.1), U2.16 (B3); also elsewhere on the board
SW8: RN1.4 (R4.1), U2.15 (B4); also elsewhere on the board
SW9: RN3.1 (R1.1), U3.18 (B1); also elsewhere on the board
SW10: RN3.2 (R2.1), U3.17 (B2); also elsewhere on the board
SW11: RN3.3 (R3.1), U3.16 (B3); also elsewhere on the board
SW12: RN3.4 (R4.1), U3.15 (B4); also elsewhere on the board
SW13: RN2.4 (R4.1), U2.11 (B8); also elsewhere on the board
SW14: RN2.3 (R3.1), U2.12 (B7); also elsewhere on the board
SW15: RN2.2 (R2.1), U2.13 (B6); also elsewhere on the board
SW16: RN2.1 (R1.1), U2.14 (B5); also elsewhere on the board

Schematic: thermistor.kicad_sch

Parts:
C82: 100nF; C_0603_1608Metric
D32: BAV99; SOT-23
J50: Conn_01x02_Pin; JST_XH_B2B-XH-A_1x02_P2.50mm_Vertical
R108, R109: 2.37k; C_0603_1608Metric
R110: 4.7k; C_0603_1608Metric

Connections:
+3.3V: D32.2 (A), R110.2; also elsewhere on the board
GND: C82.1, D32.1 (K), J50.2; also elsewhere on the board
unnamed: D32.3 (K), R108.1, R109.2
unnamed: J50.1, R108.2, R110.1
TH0: C82.2, R109.1; also elsewhere on the board

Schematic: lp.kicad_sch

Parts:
D6: LED; LED_0603_1608Metric
D7: 1N4007; D_SOD-123
J41: Conn_01x02_Pin; JST_XH_B2B-XH-A_1x02_P2.50mm_Vertical
Q2: IRLML0030; SOT-23
R64: 2.7k; R_0603_1608Metric
R65: 100; R_0603_1608Metric
R66: 10k; R_0603_1608Metric

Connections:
+24V: D7.1 (K), J41.1; also elsewhere on the board
GND: Q2.2 (S), R64.1, R66.2; also elsewhere on the board
unnamed: D6.1 (K), R64.2
unnamed: D7.2 (A), J41.2, Q2.3 (D)
unnamed: Q2.1 (G), R65.2, R66.1
OUT2: D6.2 (A), R65.1; also elsewhere on the board

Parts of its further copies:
D9: LED; LED_0603_1608Metric
D10: 1N4007; D_SOD-123
J44: Conn_01x02_Pin; JST_XH_B2B-XH-A_1x02_P2.50mm_Vertical
Q4: IRLML0030; SOT-23
R70: 2.7k; R_0603_1608Metric
R71: 100; R_0603_1608Metric
R72: 10k; R_0603_1608Metric

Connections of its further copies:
+24V: D10.1 (K), J44.1; also elsewhere on the board
GND: Q4.2 (S), R70.1, R72.2; also elsewhere on the board
unnamed: D9.1 (K), R70.2
unnamed: D10.2 (A), J44.2, Q4.3 (D)
unnamed: Q4.1 (G), R71.2, R72.1
OUT3: D9.2 (A), R71.1; also elsewhere on the board

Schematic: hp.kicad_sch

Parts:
D5: LED; LED_0603_1608Metric
J39: Conn_01x02_Pin; Molex_Micro-Fit_3.0_43045-0212_2x01_P3.00mm_Vertical
Q1: HY1904C2; DFN-8_L5.9-W5.2-P1.27-LS6.2-BL; LCSC Part C358116
R61: 3.3k; R_0603_1608Metric
R62: 100; R_0603_1608Metric
R63: 10k; R_0603_1608Metric

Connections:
+24V: J39.1; also elsewhere on the board
/Outputs/High Power 1/EN: D5.2 (A), R62.1; also elsewhere on the board
GND: Q1.1 (S), Q1.2 (S), Q1.3 (S), R61.1, R63.2; also elsewhere on the board
unnamed: D5.1 (K), R61.2
unnamed: J39.2, Q1.5 (D), Q1.6 (D), Q1.7 (D), Q1.8 (D), Q1.9 (D)
unnamed: Q1.4 (G), R62.2, R63.1
